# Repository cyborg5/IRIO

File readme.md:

#IRIO 2 - Infrared Input Output Board 

This is instead of Eagle CAD Files for a Infrared Transmitter and Receiver for Use with IRLib 2.

Uses 2 IR LEDs, 2 PNP driver transistors driven by a single NPN driver transistor. Also requires 1K ohms resistor and two 33 ohms resistors.

Has space for a TSOPxxxxx receiver and a TSMP58000 learner chip.

Open source hardware. Creative Commons Share Alike

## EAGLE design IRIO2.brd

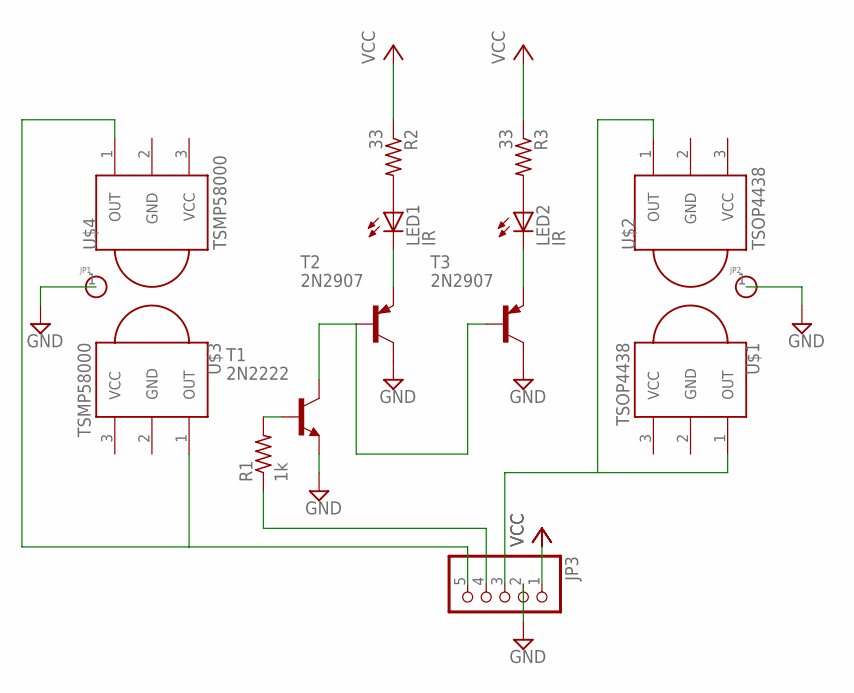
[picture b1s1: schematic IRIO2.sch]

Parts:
JP1, JP2: HOLE-DEV; HOLE-PAH
JP3: PINHD-1X5; 1X05
LED1, LED2: IR; LED3MM
R1: 1k; 0207/10
R2, R3: 33; 0204V
T1: 2N2222; TO92-EBC-OVAL
T2, T3: 2N2907; TO92-EBC-OVAL
U$1, U$2: TSOP4438; PNA460XM
U$3, U$4: TSMP58000; PNA460XM

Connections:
GND: JP1.1, JP2.1, JP3.2, T1.E, T2.C, T3.C, U$1.2 (GND), U$2.2 (GND), U$3.2 (GND), U$4.2 (GND)
unnamed: JP3.5, U$3.1 (OUT), U$4.1 (OUT)
unnamed: T1.C, T2.B, T3.B
unnamed: R1.2, T1.B
unnamed: LED2.K (C), T3.E
unnamed: LED1.K (C), T2.E
unnamed: LED2.A, R3.2
unnamed: LED1.A, R2.2
unnamed: JP3.3, U$1.1 (OUT), U$2.1 (OUT)
unnamed: JP3.4, R1.1
VCC: JP3.1, R2.1, R3.1, U$1.3 (VCC), U$2.3 (VCC), U$3.3 (VCC), U$4.3 (VCC)

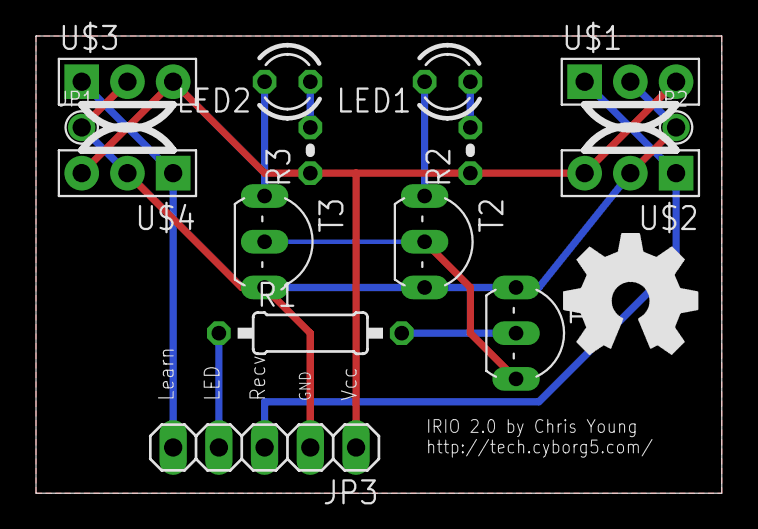
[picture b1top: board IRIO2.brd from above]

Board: 2 copper layers, 38.1 x 25.4 mm, 15 parts (0 on the bottom side), 11 nets.

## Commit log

2017-03-01 :circus_tent: Added .gitattributes & .gitignore files
2017-03-01 Initial Release version 2.0
    Initial Release version 2.0
